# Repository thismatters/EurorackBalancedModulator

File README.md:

# Balanced Modulator

The Balanced Modulator combines to audio signals to create interesting overtones, not unlike a ring modulator but lacking many sidebands.

The circuit here is based on the [Yusynth Double Balanced Modulator](https://yusynth.net/Modular/EN/RINGMOD/index.html) with minor tweaks to make it more Eurorack friendly. The changes I've made are thus:
* Selected resistors appropriate for +/-12V rails,
* Added polarity protection so that a backward power header doesn't fry anything (twin series schotty diodes: BAT54SL),
* Full surface mount design,
* Reduced module to a single balanced modulator.

The Yusynth page is a treasure trove of information about this circuit that I am too amateur to claim as my own; please read that outstanding page before using this circuit. The page provides many details and other implementations of this circuit that you may find suitable.

The KiCAD project here uses the library/footprints [found in my companion repo](https://github.com/thismatters/EurorackKiCAD).

## Width

12hp on an Intellijel 1U rack.

## Inputs

Jacks:
- Carrier Signal: `A sin(f_1 t)`
- Modulating Signal: `B sin(f_2 t)`

## Outputs

Output jack for modulated signal: `A sin((f_1 + f_2) t) + A sin((f_1 - f_2) t)`

## Adjustment

* Set up the module to be in "AC" mode (see below).
* Set a VCO to output 1000Hz sine wave and connect it to the "carrier" input.
* Connect an oscilloscope to the output of the module.
* Adjust RV2 until the module output is flat.
* Move the VCO output to the "modulating" input.
* Adjust RV1 until the module output is flat.

### Choose Operating Mode

There are three sets of jumpers for setting whether the inputs and outputs will be AC or DC coupled.
Use three jumpers to choose how the signals will be coupled.

## Vendors

There are part numbers in the [BOM](balanced-modulator.csv) for many of the parts (not for basic passives though) at the following vendors:

* [Mouser](https://www.mouser.com): Needs no introduction. Get your ICs from here (or [digikey](https://www.digikey.com)).
* [Tayda Electronics](https://www.taydaelectronics.com/): Good supplier for passive components; audio jacks, and potentiometers. Their audio jacks are slightly smaller than the thonkiconn from thonk.
* [Love My Switches](https://lovemyswitches.com/): Has [really good knobs](https://lovemyswitches.com/anodized-aluminum-knob-the-lo-fi-1-4-smooth-shaft-12-5mm-od/) to go on those potentiometers!
* [OSHPark](https://oshpark.com/): Fast and (relatively) cheap PCB manufacturer. [V0 PCB works great!](https://oshpark.com/shared_projects/MmM817Fr)

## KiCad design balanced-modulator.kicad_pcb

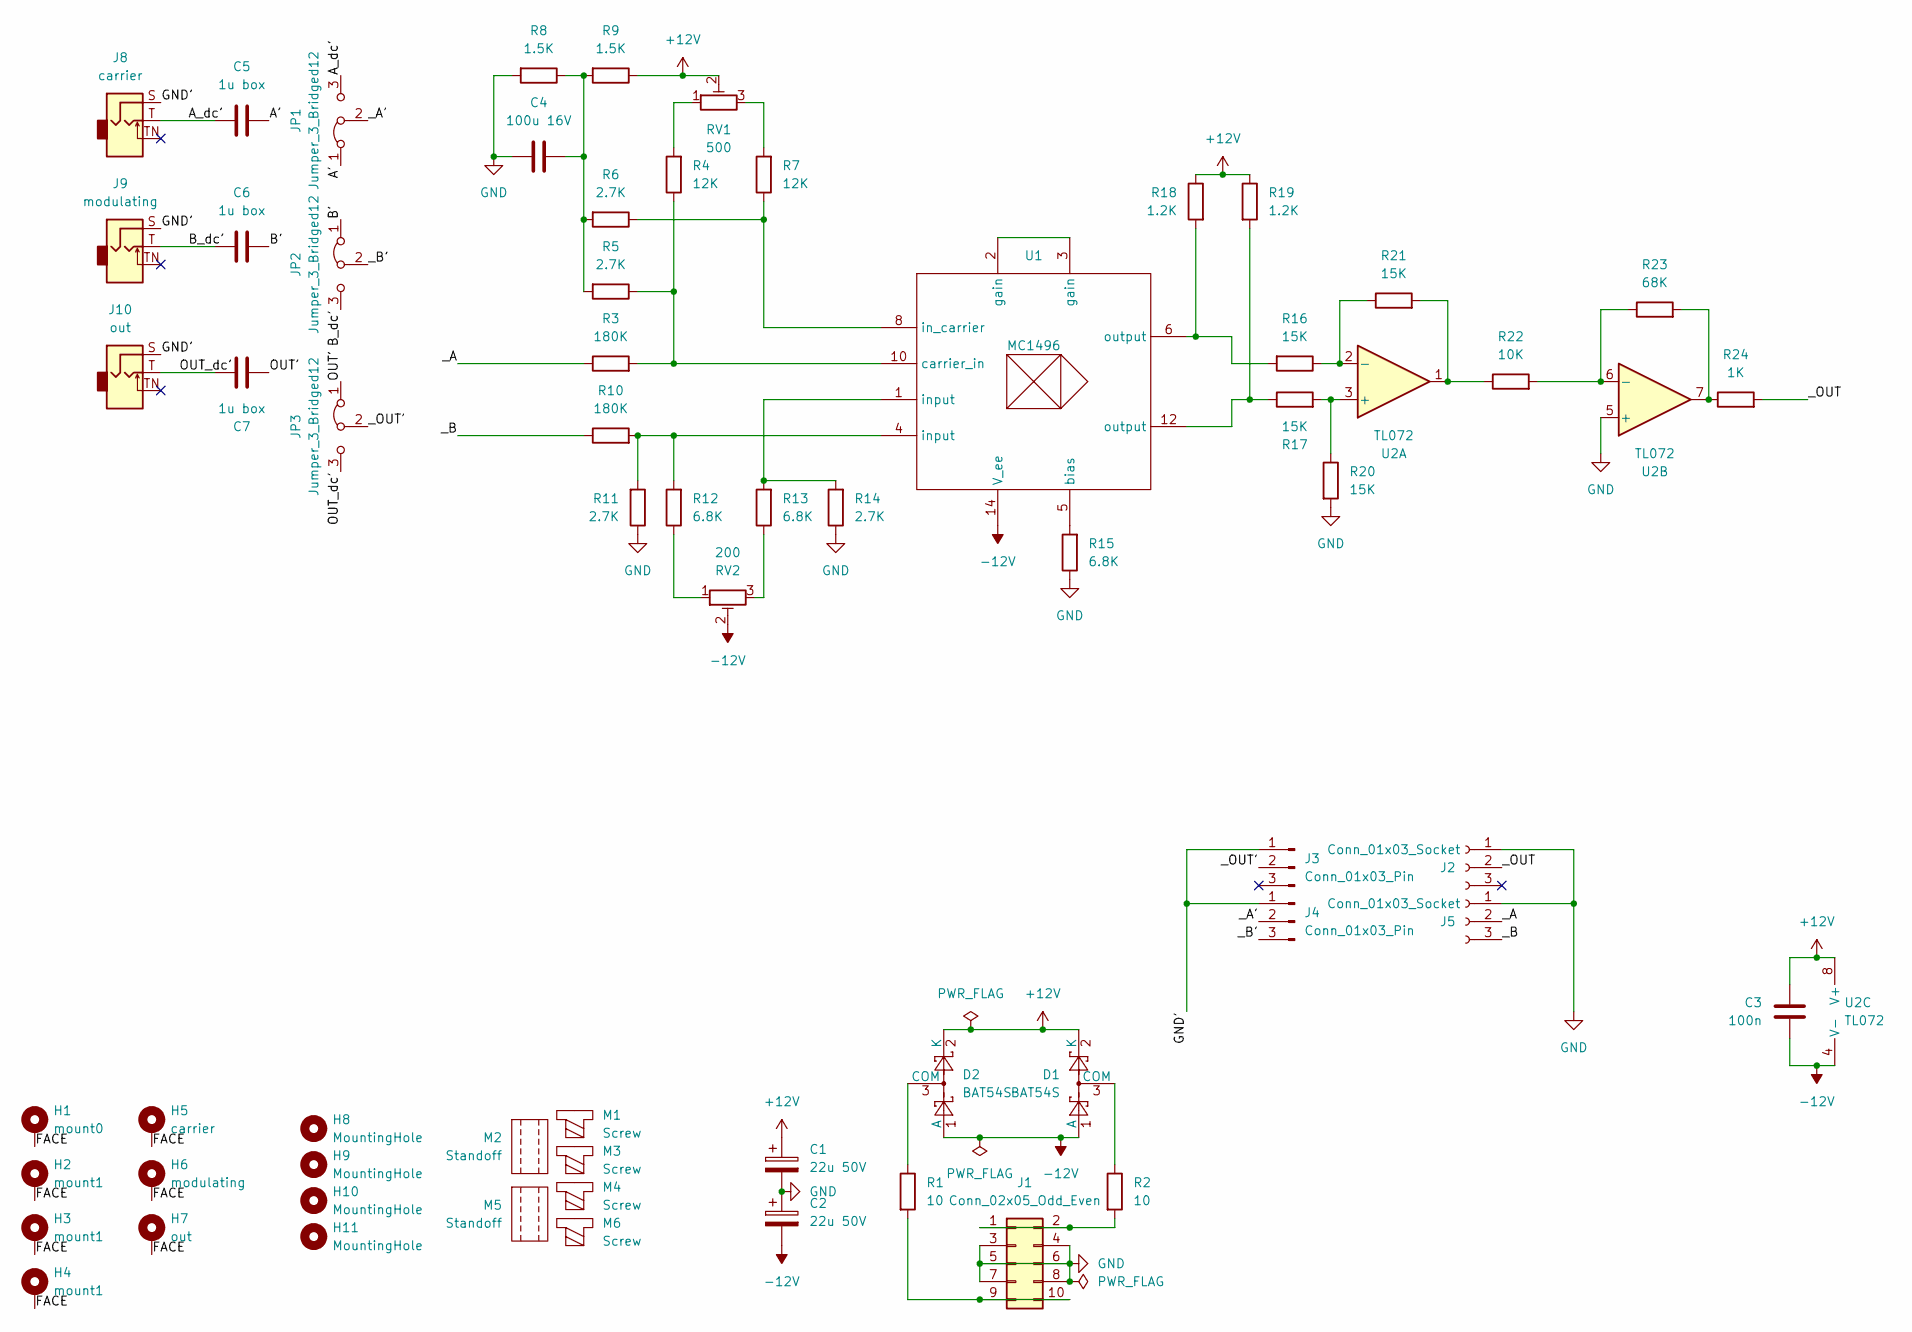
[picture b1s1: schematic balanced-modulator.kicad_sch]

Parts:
C1, C2: 22u 50V; CP_Radial_D5.0mm_P2.50mm
C3: 100n; C_0805_2012Metric
C4: 100u 16V; CP_Radial_D5.0mm_P2.50mm
C5, C6, C7: 1u box; C_Rect_Horizontal_L7.2mm_W11
D1, D2: BAT54S; SOT-23; PartNum 863-BAT54SLT1G
H1: mount0; Mech-MountingHole
H2, H3, H4: mount1; Mech-MountingHole
H5: carrier; Mech-AudioJack-Hole-Input
H6: modulating; Mech-AudioJack-Hole-Input
H7: out; Mech-AudioJack-Hole-Output
H8, H9, H10, H11: MountingHole; MountingHole_2.7mm_M2.5
J1: Conn_02x05_Odd_Even; PinHeader_2x05_P2.54mm_Vertical; PartNum A-2939
J2, J5: Conn_01x03_Socket; PinSocket_1x03_P2.54mm_Vertical
J3, J4: Conn_01x03_Pin; PinHeader_1x03_P2.54mm_Vertical
J8: carrier; AudioJack2_Tayda_A-2566; PartNum A-2566
J9: modulating; AudioJack2_Tayda_A-2566; PartNum A-2566
J10: out; AudioJack2_Tayda_A-2566; PartNum A-2566
JP1, JP2, JP3: Jumper_3_Bridged12; PinHeader_1x03_P2.54mm_Horizontal
M1, M3, M4, M6: Screw; Screw_M2.5x0.45-6mm; PartNum 36-29301-ND
M2, M5: Standoff; Standoff_M2.5x0.45-11mm; PartNum 732-10549-ND
R1, R2: 10; R_0805_2012Metric
R3, R10: 180K; R_0805_2012Metric
R4, R7: 12K; R_0805_2012Metric
R5, R6, R11, R14: 2.7K; R_0805_2012Metric
R8, R9: 1.5K; R_0805_2012Metric
R12, R13, R15: 6.8K; R_0805_2012Metric
R16, R17, R20, R21: 15K; R_0805_2012Metric
R18, R19: 1.2K; R_0805_2012Metric
R22: 10K; R_0805_2012Metric
R23: 68K; R_0805_2012Metric
R24: 1K; R_0805_2012Metric
RV1: 500; Potentiometer_Bourns_3296W_Vertical
RV2: 200; Potentiometer_Bourns_3296W_Vertical
U1: MC1496; SOIC-14_3.9x8.7mm_P1.27mm; PartNum 863-MC1496BDR2G
U2: TL072; SOIC-8_3.9x4.9mm_P1.27mm; PartNum 595-TL072CDR

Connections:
+12V: C1.1, C3.1, D1.2 (K), D2.2 (K), R9.1, R18.1, R19.1, RV1.2, U2.8 (V+)
-12V: C2.2, C3.2, D1.1 (A), D2.1 (A), RV2.2, U1.14 (V_ee), U2.4 (V-)
/A': C5.1, JP1.1 (A)
/A_dc': C5.2, J8.T, JP1.3 (B)
/B': C6.1, JP2.1 (A)
/B_dc': C6.2, J9.T, JP2.3 (B)
/FACE: H1.1, H2.1, H3.1, H4.1, H5.1, H6.1, H7.1
/GND': J3.1, J4.1, J8.S, J9.S, J10.S
/OUT': C7.2, JP3.1 (A)
/OUT_dc': C7.1, J10.T, JP3.3 (B)
/_A: J5.2, R3.1
/_A': J4.2, JP1.2 (C)
/_B: J5.3, R10.1
/_B': J4.3, JP2.2 (C)
/_OUT: J2.2, R24.2
/_OUT': J3.2, JP3.2 (C)
GND: C1.2, C2.1, C4.1, J1.3, J1.4, J1.5, J1.6, J1.7, J1.8, J2.1, J5.1, R8.2, R11.1, R14.1, R15.1, R20.2, U2.5 (+)
unnamed: C4.2, R5.2, R6.2, R8.1, R9.2
unnamed: D1.3 (COM), R2.1
unnamed: D2.3 (COM), R1.1
unnamed: J1.1, J1.2, R2.2
unnamed: J1.9, J1.10, R1.2
unnamed: R4.2, RV1.1
unnamed: R7.2, RV1.3
unnamed: R10.2, R11.2, R12.2, U1.4 (input)
unnamed: R12.1, RV2.1
unnamed: R13.1, RV2.3
unnamed: R13.2, R14.2, U1.1 (input)
unnamed: R16.2, R18.2, U1.6 (output)
unnamed: R17.1, R19.2, U1.12 (output)
unnamed: R21.2, R22.1, U2.1
unnamed: R23.2, R24.1, U2.7
unnamed: R15.2, U1.5 (bias)
unnamed: R3.2, R4.1, R5.1, U1.10 (carrier_in)
unnamed: U1.2 (gain), U1.3 (gain)
unnamed: R6.1, R7.1, U1.8 (in_carrier)
unnamed: R17.2, R20.1, U2.3 (+)
unnamed: R16.1, R21.1, U2.2 (-)
unnamed: R22.2, R23.1, U2.6 (-)

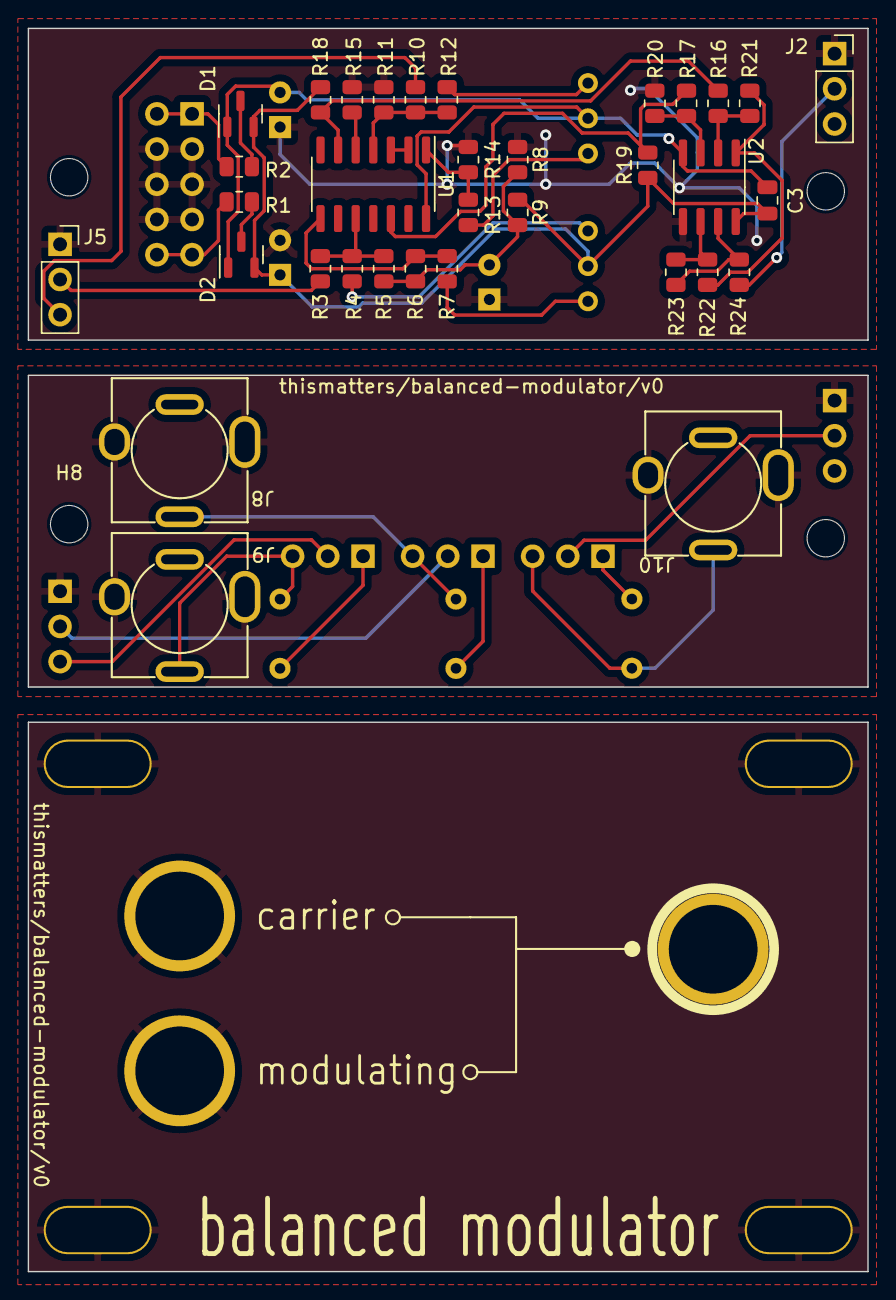
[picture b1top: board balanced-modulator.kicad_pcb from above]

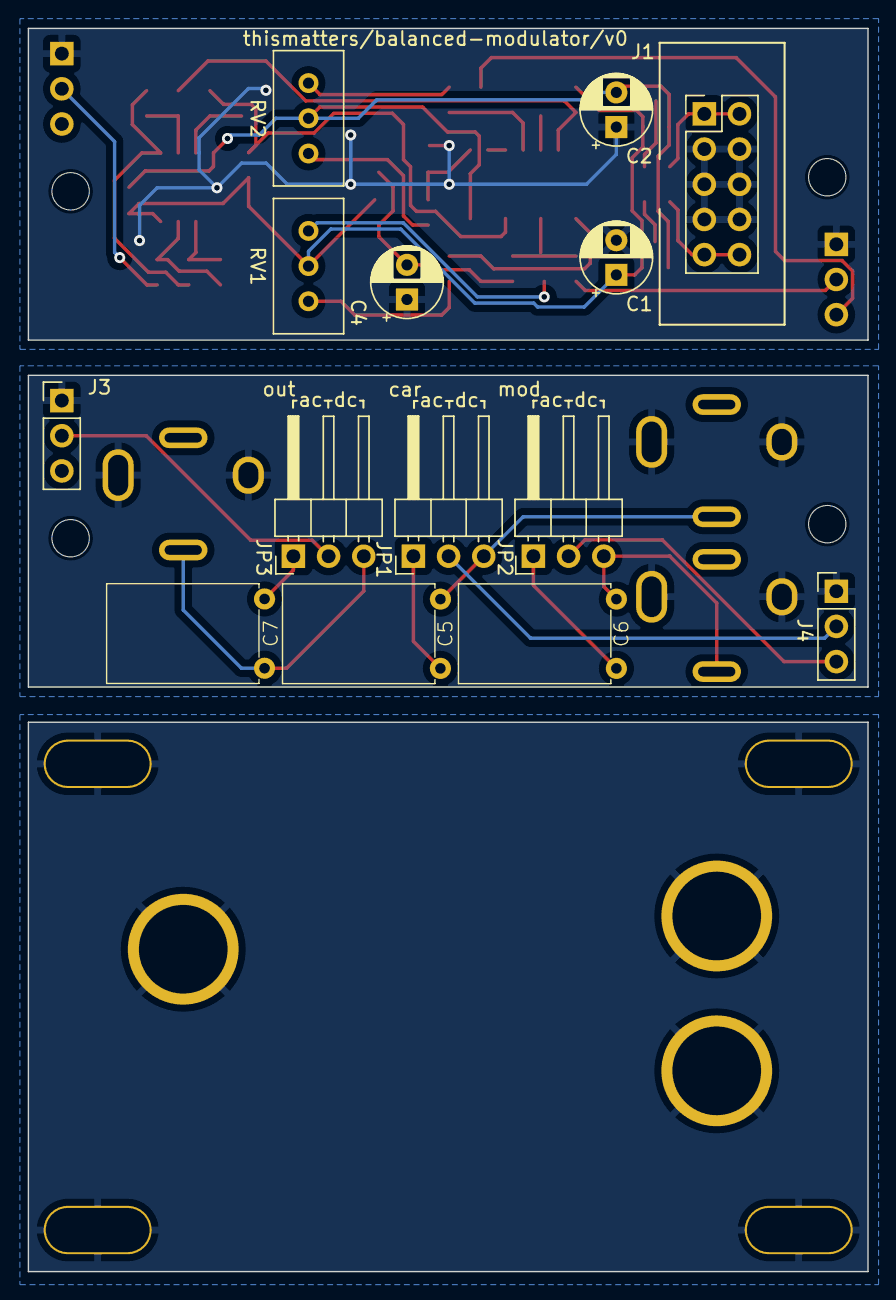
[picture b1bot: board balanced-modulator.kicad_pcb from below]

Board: 2 copper layers, 60.6 x 89.7 mm, 59 parts (14 on the bottom side), 39 nets.

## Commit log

2024-12-29 board + readme
2024-12-29 more doc
2025-01-01 adding part number
2025-01-23 ready for v0 manu
2025-03-01 prototype built
